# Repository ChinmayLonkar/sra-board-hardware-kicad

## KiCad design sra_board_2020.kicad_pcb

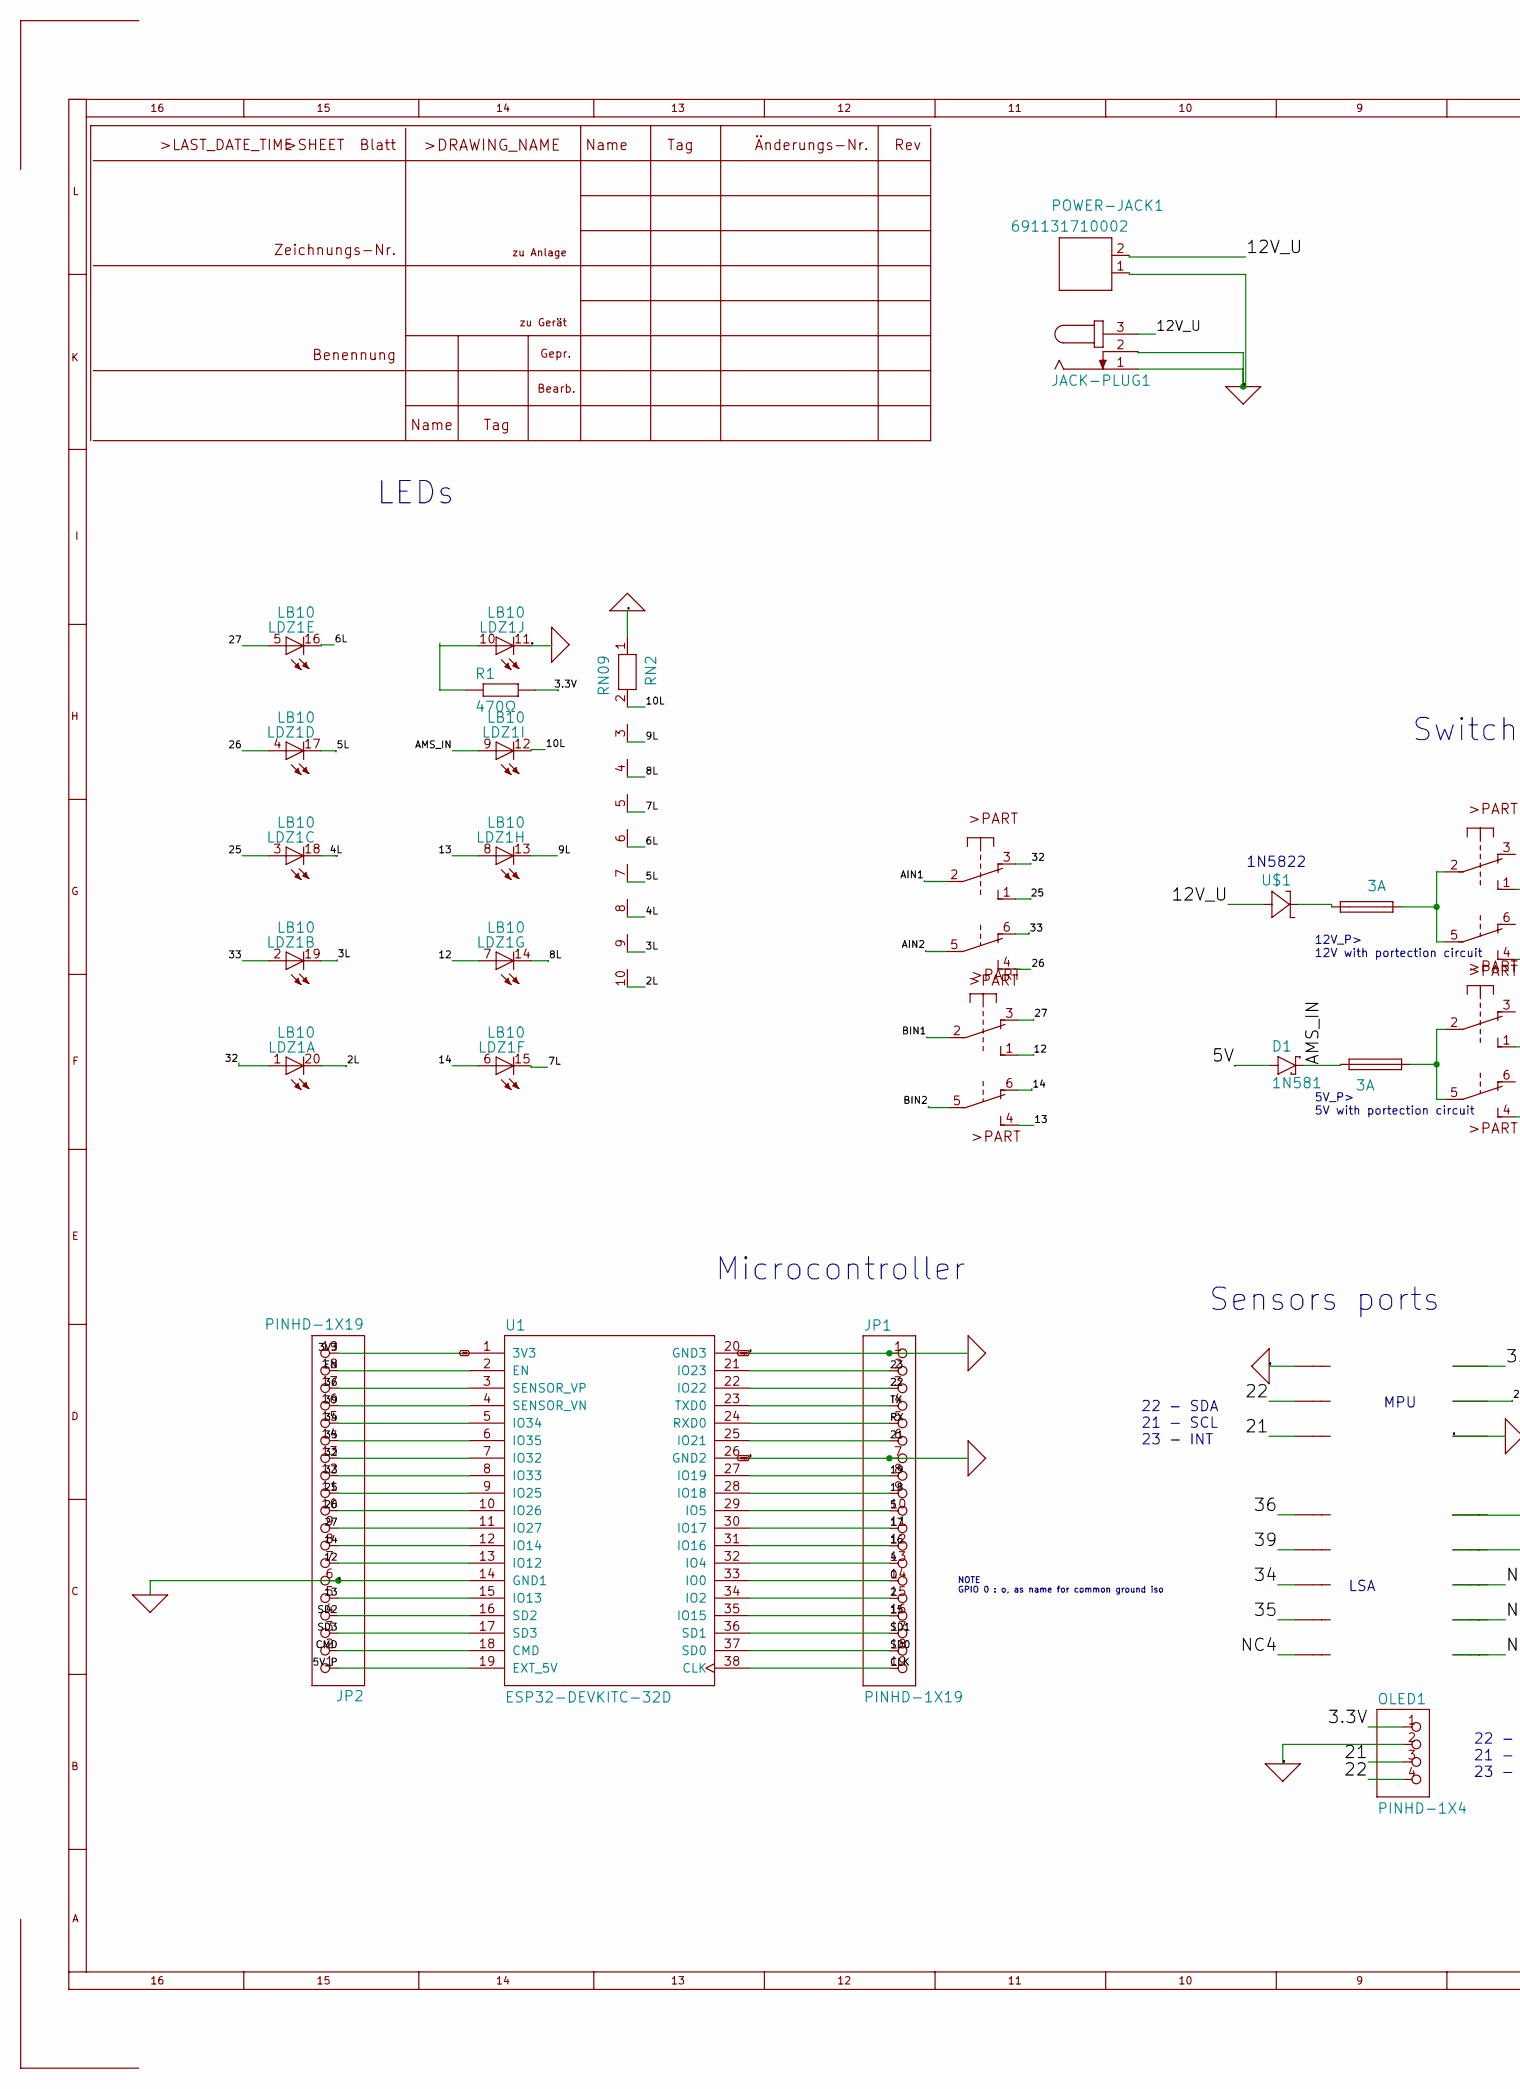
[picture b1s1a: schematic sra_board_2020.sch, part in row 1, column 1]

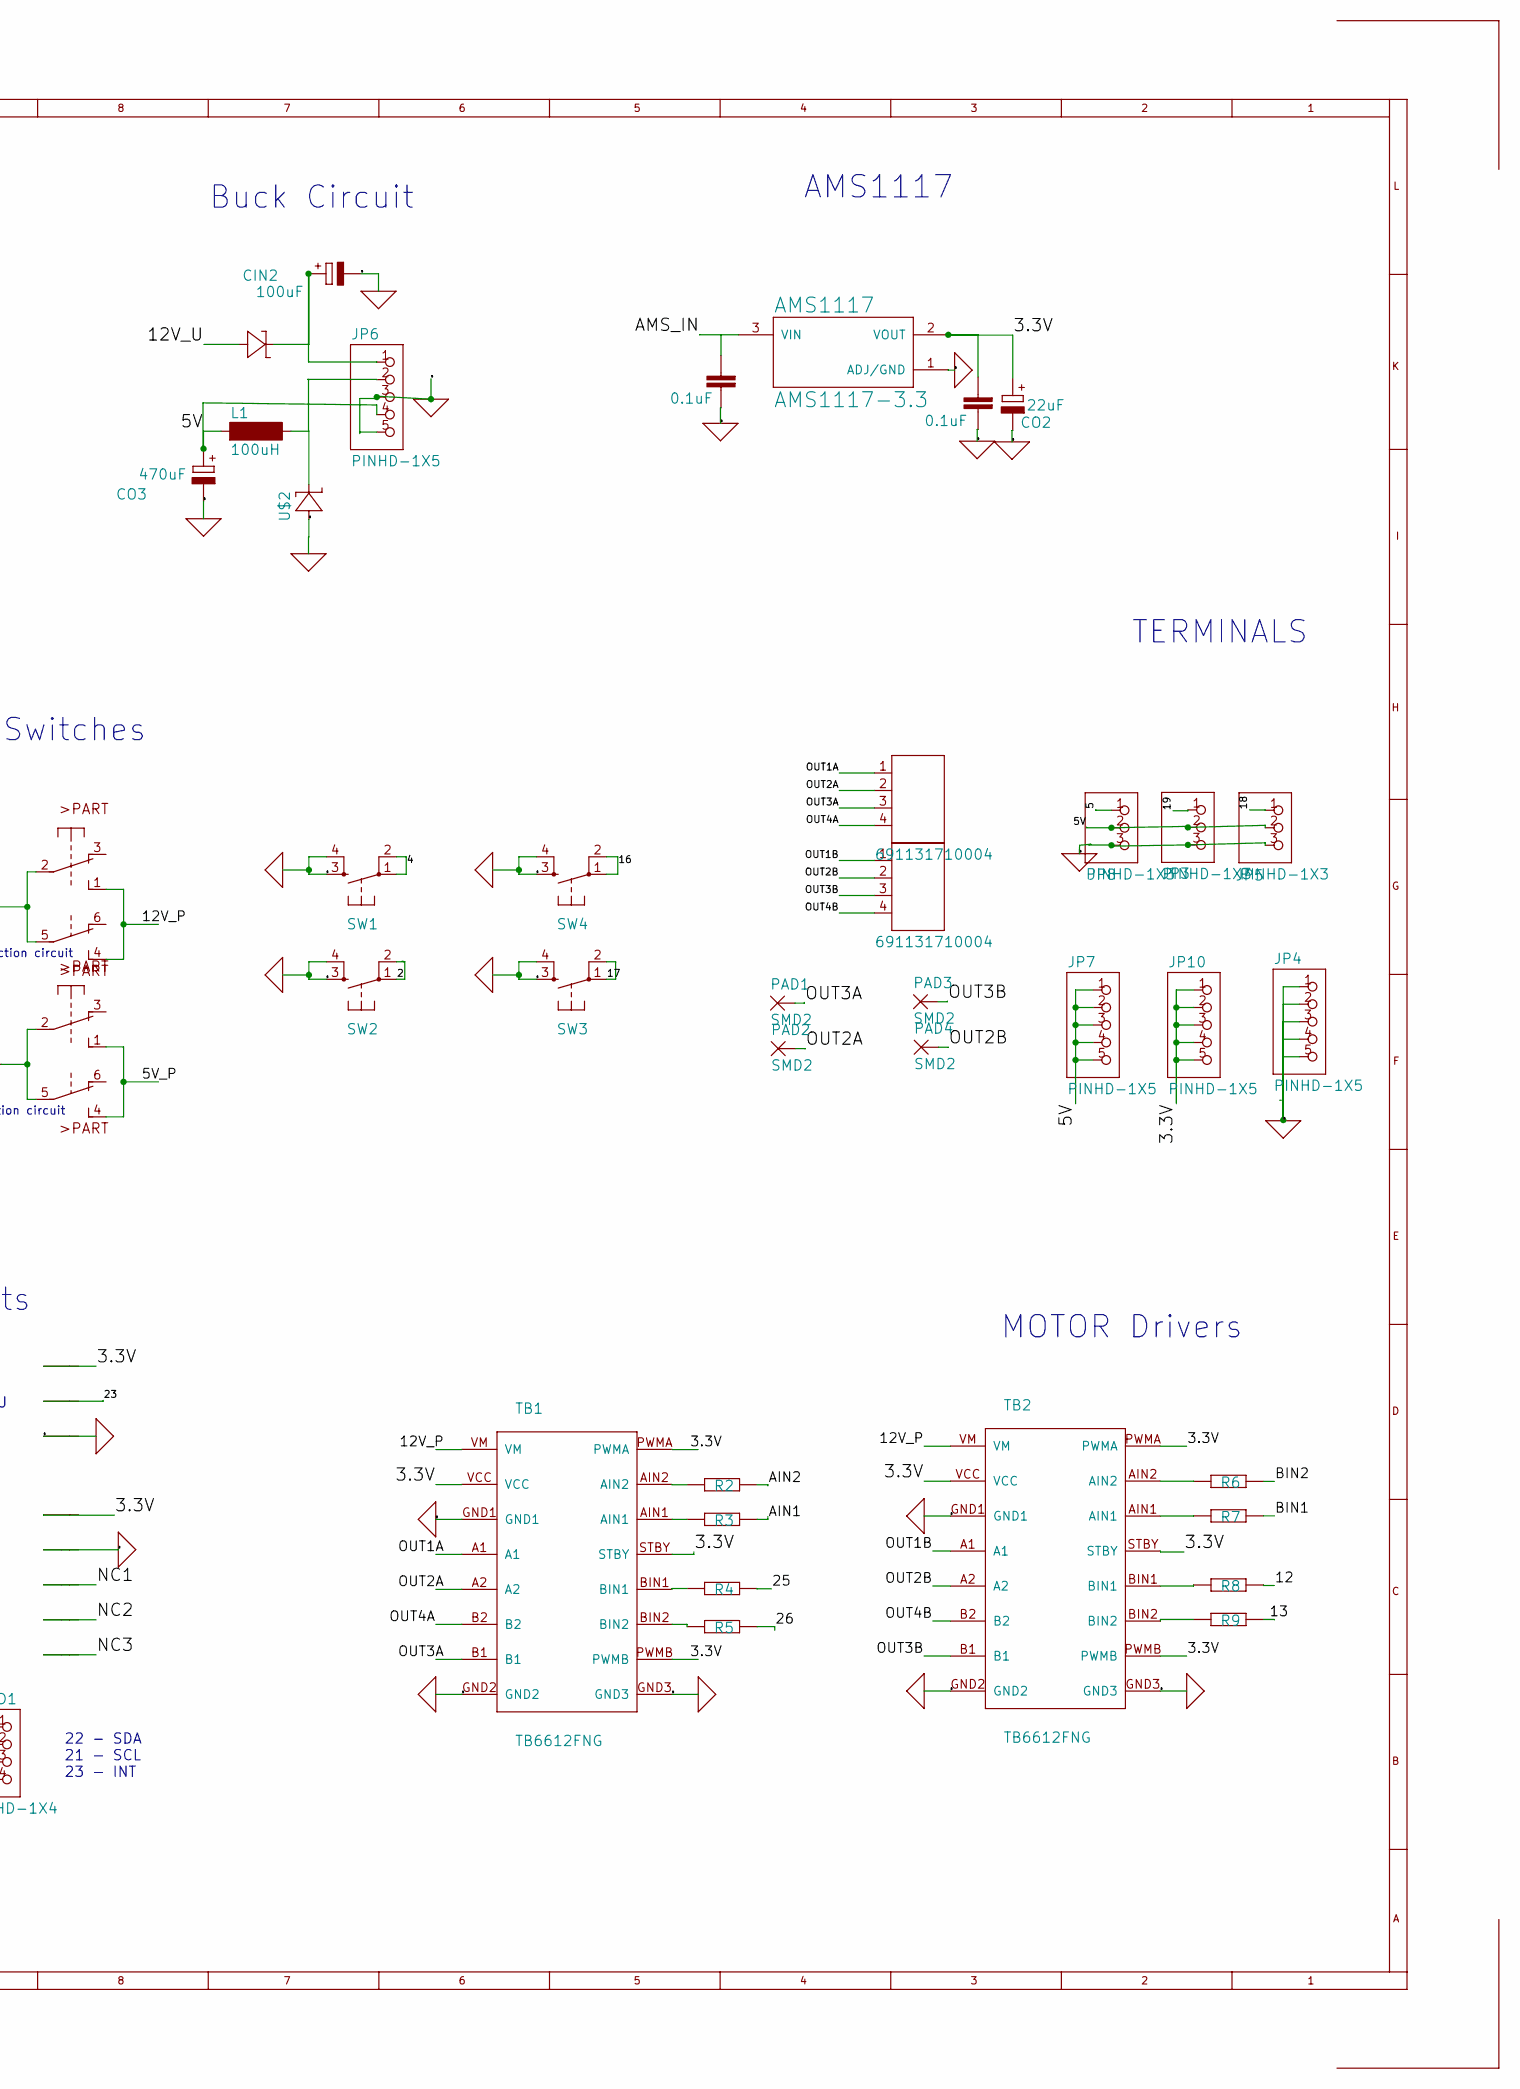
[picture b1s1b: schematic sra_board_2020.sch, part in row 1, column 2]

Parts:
12V1: 691131710002
AMS1117: AMS1117-3.3; SOT229P700X180-4N
CIN1: 0.1uF; C5B2.5
CIN2: 100uF; E2,5-6
CO1: 0.1uF; C5B2.5
CO2: 22uF; E2,5-6
CO3: 470uF; E3,5-10
D1: 1N581; DO41-7.6
F2, F3: 3A; SH25
J1, J2: 691131710004
JP1, JP2: PINHD-1X19; 1X19
JP3, JP5, JP8: PINHD-1X3; 1X03
JP4, JP6, JP7, JP10: PINHD-1X5; 1X05
L1: 100uH; SD12K100
LDZ1: LB10
LINE-SENSOR1: 057-010-1
MCU-S/W1: 9077-2
MOTOR-S/W1: 9077-2
OLED1: PINHD-1X4; 1X04
PAD1, PAD2, PAD3, PAD4: SMD2; SMD1,27-2,54
POWER-JACK1: JACK-PLUG1; SPC4078
R1: 470Ω; 0204_7
R2, R3, R4, R5, R6, R7, R8, R9: 1KΩ; 0204_7
RN2: RN09; RN-10
SW1, SW2, SW3, SW4: DTS-6
TB1, TB2: TB6612FNG
TB_A1: 9077-2
TB_B1: 9077-2
U1: ESP32-DEVKITC-32D; MODULE_ESP32-DEVKITC-32D
U$1, U$2: 1N5399_SQUARE; C2673
U$3: 1N5399_ROUND; D-10
X1: 057-006-1

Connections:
0: 12V1.1, AMS1117.1 (ADJ/GND), CIN1.1, CIN2.-, CO1.1, CO2.-, CO3.-, JP1.1, JP1.7, JP2.6, JP3.3, JP4.1, JP4.2, JP4.3, JP4.4, JP5.3, JP6.3, JP6.5, JP8.3, LDZ1.11 (C), LINE-SENSOR1.4, OLED1.2, POWER-JACK1.1, POWER-JACK1.2, RN2.1, SW1.3, SW1.4, SW2.3, SW2.4, SW3.3, SW3.4, SW4.3, SW4.4, TB1.GND1, TB1.GND2, TB1.GND3, TB2.GND1, TB2.GND2, TB2.GND3, U1.14 (GND1), U$2.A, X1.1, X1.6
3V3: U1.1 (3V3)
/2: SW2.1, SW2.2
/2L: LDZ1.20 (C), RN2.10
/3.3V: AMS1117.2 (VOUT), CO1.2, CO2.+, JP10.1, JP10.2, JP10.3, JP10.4, JP10.5, LINE-SENSOR1.2, OLED1.1, R1.2, TB1.PWMB, TB1.STBY, TB2.PWMB, TB2.STBY, X1.2
/3L: LDZ1.19 (C), RN2.9
/4: SW1.1, SW1.2
/4L: LDZ1.18 (C), RN2.8
/5: JP8.1
/5L: LDZ1.17 (C), RN2.7
/5V: CO3.+, D1.A, JP3.2, JP5.2, JP6.4, JP7.1, JP7.2, JP7.3, JP7.4, JP7.5, JP8.2, L1.1
/5V_P: JP2.1, MCU-S/W1.1 (S), MCU-S/W1.4 (S), U1.19 (EXT_5V)
/6L: LDZ1.16 (C), RN2.6
/7L: LDZ1.15 (C), RN2.5
/8L: LDZ1.14 (C), RN2.4
/9L: LDZ1.13 (C), RN2.3
/10L: LDZ1.12 (C), RN2.2
/12: JP2.7, LDZ1.7 (A), R8.2, TB_B1.1 (S), U1.13 (IO12)
/12V_P: MOTOR-S/W1.1 (S), MOTOR-S/W1.4 (S)
/12V_U: 12V1.2, POWER-JACK1.3, U$1.A, U$3.A
/13: JP2.5, LDZ1.8 (A), R9.2, TB_B1.4 (S), U1.15 (IO13)
/14: JP2.8, LDZ1.6 (A), TB_B1.6 (O), U1.12 (IO14)
/16: SW4.1, SW4.2
/17: SW3.1, SW3.2
/18: JP1.9, JP5.1
/19: JP1.8, JP3.1
/21: JP1.6, OLED1.3, X1.5
/22: JP1.3, OLED1.4, X1.3
/23: JP1.2, X1.4
/25: LDZ1.3 (A), R4.2, TB_A1.1 (S)
/26: JP2.10, LDZ1.4 (A), R5.2, TB_A1.4 (S), U1.10 (IO26)
/27: JP2.9, LDZ1.5 (A), TB_B1.3 (O), U1.11 (IO27)
/32: LDZ1.1 (A), TB_A1.3 (O)
/33: LDZ1.2 (A), TB_A1.6 (O)
/34: LINE-SENSOR1.5
/35: LINE-SENSOR1.7
/36: LINE-SENSOR1.1
/39: LINE-SENSOR1.3
/AIN1: R3.2, TB_A1.2
/AIN2: R2.2, TB_A1.5
/AMS_IN: AMS1117.3 (VIN), D1.C, F2.2, LDZ1.9 (A)
/BIN1: R7.2, TB_B1.2
/BIN2: R6.2, TB_B1.5
/CMD: JP2.2, U1.18 (CMD)
/NC1: LINE-SENSOR1.6
/NC2: LINE-SENSOR1.8
/NC3: LINE-SENSOR1.10
/NC4: LINE-SENSOR1.9
/OUT1A: J1.1, TB1.A1
/OUT1B: J2.1, TB2.A1
/OUT2A: J1.2, PAD2.1, TB1.A2
/OUT2B: J2.2, PAD4.1, TB2.A2
/OUT3A: J1.3, PAD1.1, TB1.B1
/OUT3B: J2.3, PAD3.1, TB2.B1
/OUT4A: J1.4, TB1.B2
/OUT4B: J2.4, TB2.B2
/RX: JP1.5
/SD2: JP2.4, U1.16 (SD2)
/SD3: JP2.3, U1.17 (SD3)
/TX: JP1.4
GND2: U1.26 (GND2)
GND3: U1.20 (GND3)
unnamed: CIN2.+, JP6.1, U$3.C
unnamed: F2.1, MCU-S/W1.2, MCU-S/W1.5
unnamed: F3.1, U$1.C
unnamed: F3.2, MOTOR-S/W1.2, MOTOR-S/W1.5
unnamed: L1.2, U$2.C
unnamed: LDZ1.10 (A), R1.1
unnamed: R3.1, TB1.AIN1
unnamed: R4.1, TB1.BIN1
unnamed: R5.1, TB1.BIN2
unnamed: R7.1, TB2.AIN1
unnamed: R8.1, TB2.BIN1
unnamed: R9.1, TB2.BIN2

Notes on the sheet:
TERMINALS
MOTOR Drivers
Microcontroller
Buck Circuit
Switches
12V_P> 12V with portection circuit
5V_P> 5V with portection circuit
Sensors ports
MPU
LSA
NOTE GPIO 0 : o, as name for common ground iso
AMS1117
LEDs
1N5822
22 - SDA 21 - SCL 23 - INT

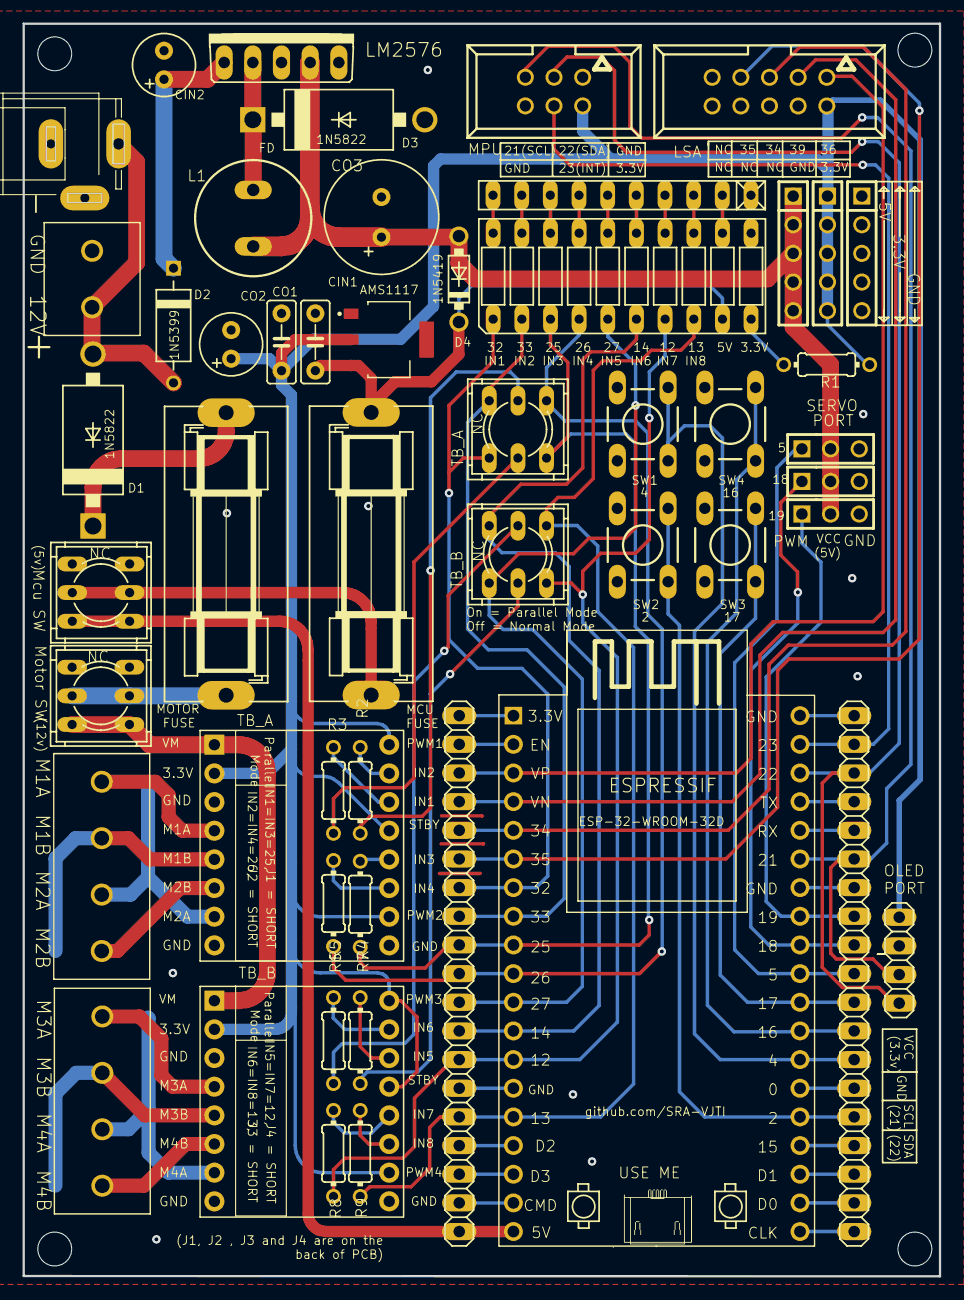
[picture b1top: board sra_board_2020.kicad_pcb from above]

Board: 2 copper layers, 81.2 x 111.0 mm, 59 parts (0 on the bottom side), 60 nets.

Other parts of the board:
@HOLE0, @HOLE1, @HOLE2, @HOLE3: (no value)

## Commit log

2022-01-07 Kicad Files for SRA-Board
